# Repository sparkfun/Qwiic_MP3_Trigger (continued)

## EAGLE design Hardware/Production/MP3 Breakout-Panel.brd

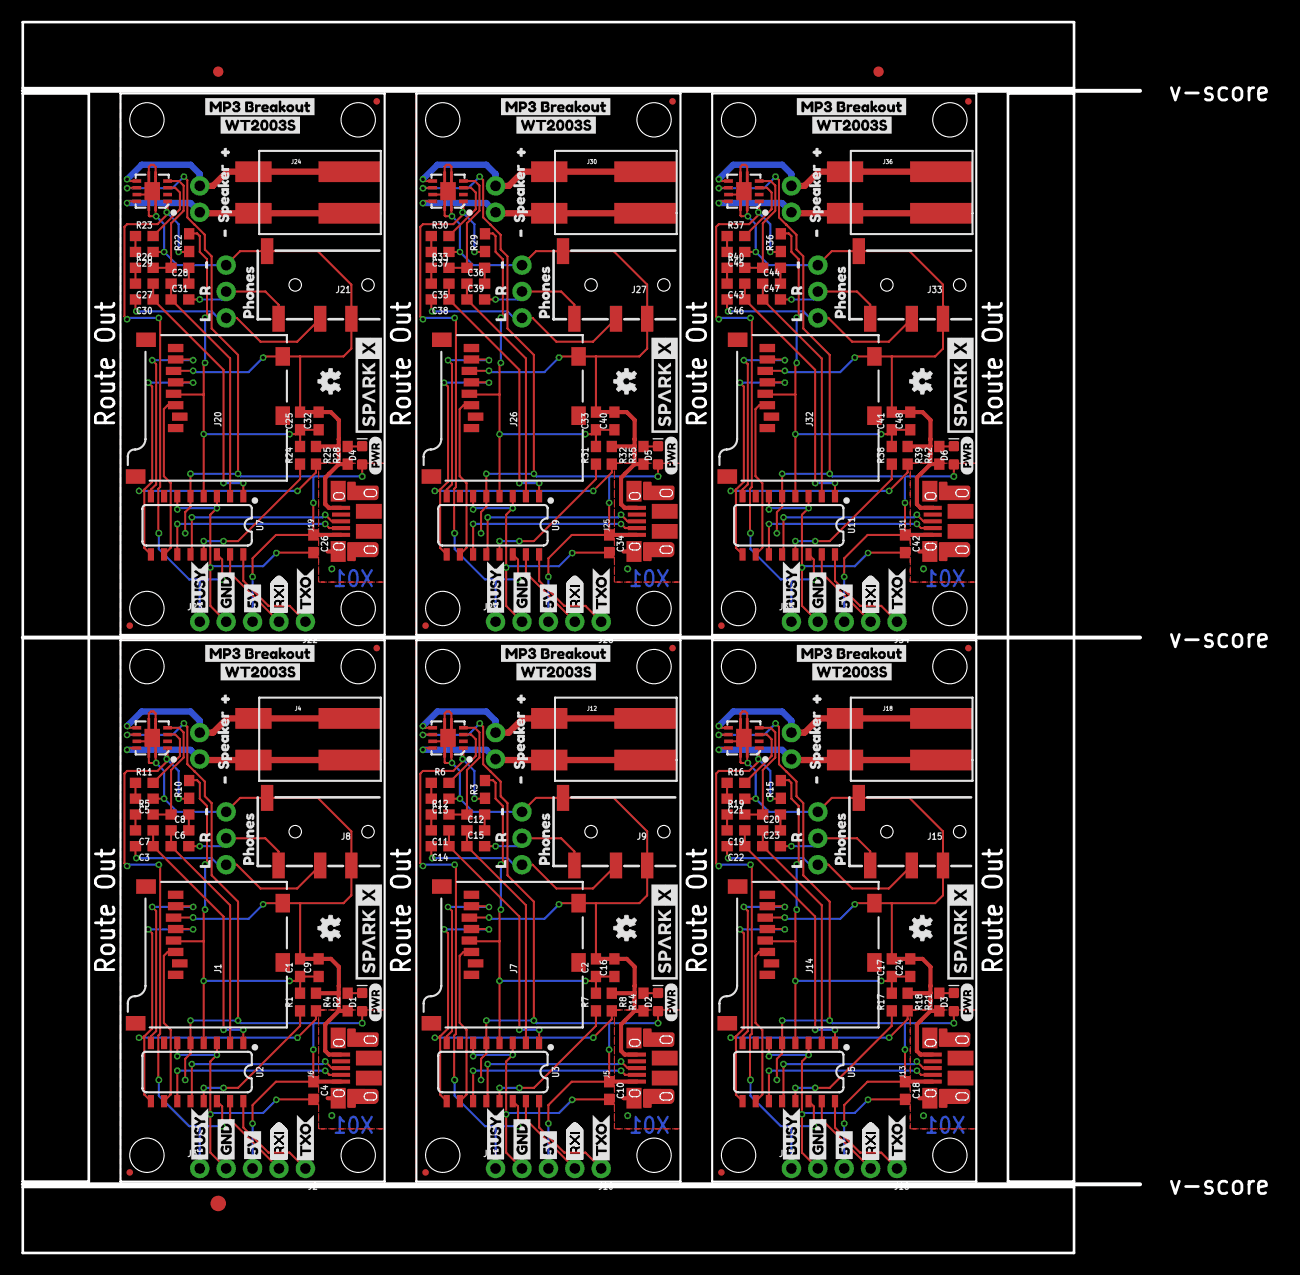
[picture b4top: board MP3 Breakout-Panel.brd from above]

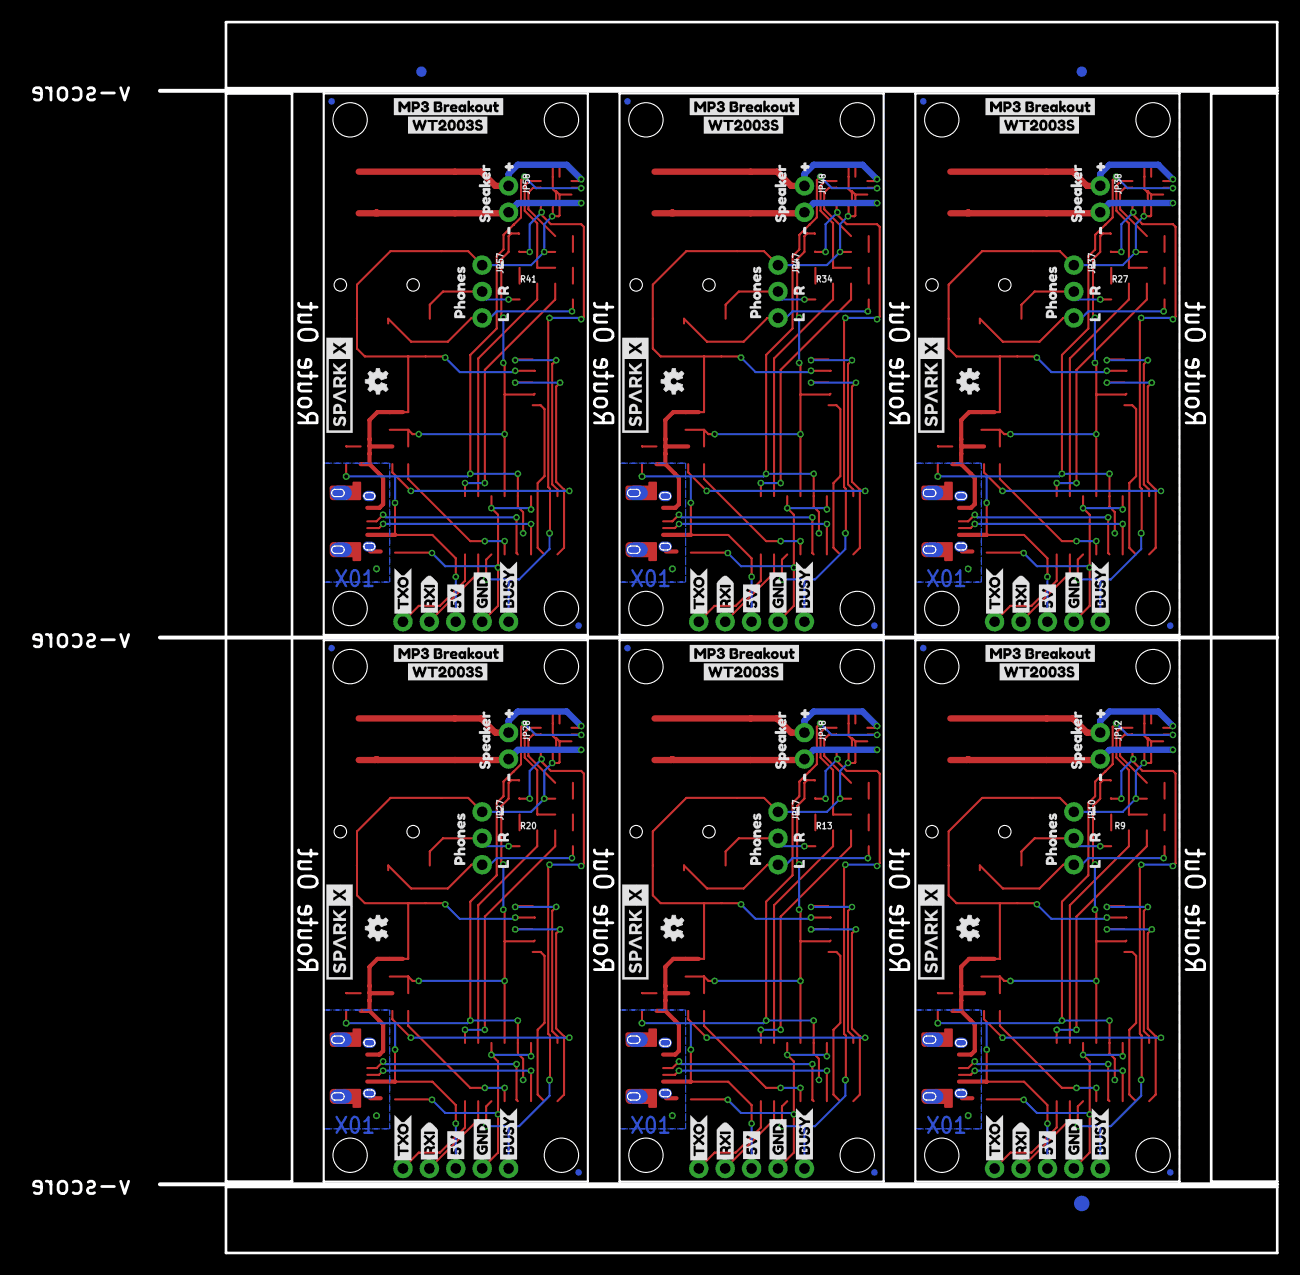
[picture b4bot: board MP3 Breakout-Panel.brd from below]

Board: 2 copper layers, 107.4 x 118.4 mm, 414 parts (123 on the bottom side), 150 nets.

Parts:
C1, C2, C17, C25, C33, C41: 10uF; 0603
C3, C6, C14, C15, C22, C23, C30, C31, C38, C39, C46, C47: 0.22uF; 0603
C4, C5, C9, C10, C13, C16, C18, C21, C24, C26, C29, C32, C34, C37, C40, C42, C45, C48: 1.0uF; 0603
C7, C8, C11, C12, C19, C20, C27, C28, C35, C36, C43, C44: 0.1uF; 0603
D1, D2, D3, D4, D5, D6: RED; LED-0603
E$1, E$2, E$3, E$4: FIDUCIAL-1X2
E$5, E$6: FIDUCIAL-1.5X3
J1, J7, J14, J20, J26, J32: MICRO-SD; MICRO-SD-SOCKET
J2, J10, J16, J22, J28, J34: Header; 1X04_NO_SILK
J3, J11, J17, J23, J29, J35: 1X01_NO_SILK
J4, J12, J18, J24, J30, J36: Poke-Home; 1X02_POKEHOME
J5, J6, J13, J19, J25, J31: USB-MICROB-PTH-MILL
J8, J9, J15, J21, J27, J33: 3.5mm Audio; AUDIO_JACK_3.5MM_TRRS_SMD_RA
JP1, JP2, JP5, JP6, JP9, JP14, JP15, JP16, JP23, JP24, JP25, JP26, JP33, JP34, JP35, JP36, JP43, JP44, JP45, JP46, JP53, JP54, JP55, JP56: FIDUCIALUFIDUCIAL; MICRO-FIDUCIAL
JP3, JP4, JP7, JP8, JP11, JP13, JP19, JP20, JP21, JP22, JP29, JP30, JP31, JP32, JP39, JP40, JP41, JP42, JP49, JP50, JP51, JP52, JP59, JP60: STAND-OFF
JP10, JP17, JP27, JP37, JP47, JP57: PTH; 1X03_NO_SILK
JP12, JP18, JP28, JP38, JP48, JP58: PTH; 1X02_NO_SILK
LOGO1, LOGO3, LOGO5, LOGO7, LOGO9, LOGO11: OSHW-LOGOMINI; OSHW-LOGO-MINI
LOGO2, LOGO4, LOGO6, LOGO8, LOGO10, LOGO12: OSHW-LOGOMINI; OSHW-LOGO-MINI@1
R1, R3, R5, R7, R9, R10, R12, R13, R15, R17, R19, R20, R22, R24, R26, R27, R29, R31, R33, R34, R36, R38, R40, R41: 10k; 0603
R2, R14, R21, R28, R35, R42: 1k; 0603
R4, R8, R18, R25, R32, R39: 2.2k; 0603
R6, R11, R16, R23, R30, R37: 100k; 0603
U1, U4, U6, U8, U10, U12: TPA2005D1; QFN-8_PAD
U2, U3, U5, U7, U9, U11: WT2003S; SO16
U$1, U$22, U$31, U$45, U$66, U$77, U$98, U$109, U$130, U$141, U$162, U$173: GND1
U$2, U$5, U$11, U$49, U$65, U$81, U$97, U$113, U$129, U$145, U$161, U$177: SPARKX-LOGO4; SPARKX-MEDIUM
U$3, U$38, U$41, U$52, U$73, U$84, U$105, U$116, U$137, U$148, U$169, U$180: L12
U$4, U$37, U$39, U$53, U$72, U$85, U$104, U$117, U$136, U$149, U$168, U$181: R11
U$6, U$9, U$43, U$48, U$75, U$80, U$107, U$112, U$139, U$144, U$171, U$176: TXO0
U$7, U$8, U$23, U$44, U$46, U$47, U$76, U$78, U$79, U$108, U$110, U$111, U$140, U$142, U$143, U$172, U$174, U$175: RXI0
U$10, U$15, U$21, U$25, U$33, U$35, U$54, U$58, U$68, U$70, U$86, U$90, U$100, U$102, U$118, U$122, U$132, U$134, U$150, U$154, U$164, U$166, U$182, U$186: #6
U$12, U$24, U$59, U$60, U$91, U$92, U$123, U$124, U$155, U$156, U$187, U$188: MP3_BREAKOUT0
U$13, U$14, U$50, U$51, U$82, U$83, U$114, U$115, U$146, U$147, U$178, U$179: BUSY0
U$16, U$40, U$42, U$55, U$74, U$87, U$106, U$119, U$138, U$151, U$170, U$183: PHONES0
U$17, U$32, U$67, U$99, U$131, U$163: PWR-()-03
U$18, U$20, U$34, U$56, U$69, U$88, U$101, U$120, U$133, U$152, U$165, U$184: SPEAKER1
U$19, U$28, U$36, U$57, U$71, U$89, U$103, U$121, U$135, U$153, U$167, U$185: #5
U$26, U$27, U$61, U$62, U$93, U$94, U$125, U$126, U$157, U$158, U$189, U$190: WT2003S0
U$29, U$30, U$63, U$64, U$95, U$96, U$127, U$128, U$159, U$160, U$191, U$192: 5V0

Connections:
5V: C4.1, D1.A, J2.3, J6.VBUS, U1.6, U2.5
5V1: C10.1, D2.A, J5.VBUS, J10.3, U3.5, U4.6
5V2: C18.1, D3.A, J13.VBUS, J16.3, U5.5, U6.6
5V3: C26.1, D4.A, J19.VBUS, J22.3, U7.5, U8.6
5V4: C34.1, D5.A, J25.VBUS, J28.3, U9.5, U10.6
5V5: C42.1, D6.A, J31.VBUS, J34.3, U11.5, U12.6
!SDN: J3.1, R10.1, U1.1, U2.14
!SDN1: J11.1, R3.1, U3.14, U4.1
!SDN2: J17.1, R15.1, U5.14, U6.1
!SDN3: J23.1, R22.1, U7.14, U8.1
!SDN4: J29.1, R29.1, U9.14, U10.1
!SDN5: J35.1, R36.1, U11.14, U12.1
AC-L: C3.2, J8.RING1, JP10.3
AC-L1: C14.2, J9.RING1, JP17.3
AC-L2: C22.2, J15.RING1, JP27.3
AC-L3: C30.2, J21.RING1, JP37.3
AC-L4: C38.2, J27.RING1, JP47.3
AC-L5: C46.2, J33.RING1, JP57.3
AC-R: C6.2, J8.TIP, JP10.2
AC-R1: C15.2, J9.TIP, JP17.2
AC-R2: C23.2, J15.TIP, JP27.2
AC-R3: C31.2, J21.TIP, JP37.2
AC-R4: C39.2, J27.TIP, JP47.2
AC-R5: C47.2, J33.TIP, JP57.2
ADKEY: R1.1, U2.13
ADKEY1: R7.1, U3.13
ADKEY2: R17.1, U5.13
ADKEY3: R24.1, U7.13
ADKEY4: R31.1, U9.13
ADKEY5: R38.1, U11.13
D+: J6.D+, U2.12
D+1: J5.D+, U3.12
D+2: J13.D+, U5.12
D+3: J19.D+, U7.12
D+4: J25.D+, U9.12
D+5: J31.D+, U11.12
D-: J6.D-, U2.11
D-1: J5.D-, U3.11
D-2: J13.D-, U5.11
D-3: J19.D-, U7.11
D-4: J25.D-, U9.11
D-5: J31.D-, U11.11
GND: C1.2, C4.2, C5.1, C9.2, J1.CD1, J1.GND, J2.4, J6.GND, J8.EARTH, J8.RING2, JP10.1, R2.1, R4.1, U1.7, U1.9, U1.10, U1.11, U1.12, U1.13, U2.3, U2.6
GND1: C2.2, C10.2, C13.1, C16.2, J5.GND, J7.CD1, J7.GND, J9.EARTH, J9.RING2, J10.4, JP17.1, R8.1, R14.1, U3.3, U3.6, U4.7, U4.9, U4.10, U4.11, U4.12, U4.13
GND2: C17.2, C18.2, C21.1, C24.2, J13.GND, J14.CD1, J14.GND, J15.EARTH, J15.RING2, J16.4, JP27.1, R18.1, R21.1, U5.3, U5.6, U6.7, U6.9, U6.10, U6.11, U6.12, U6.13
GND3: C25.2, C26.2, C29.1, C32.2, J19.GND, J20.CD1, J20.GND, J21.EARTH, J21.RING2, J22.4, JP37.1, R25.1, R28.1, U7.3, U7.6, U8.7, U8.9, U8.10, U8.11, U8.12, U8.13
GND4: C33.2, C34.2, C37.1, C40.2, J25.GND, J26.CD1, J26.GND, J27.EARTH, J27.RING2, J28.4, JP47.1, R32.1, R35.1, U9.3, U9.6, U10.7, U10.9, U10.10, U10.11, U10.12, U10.13
GND5: C41.2, C42.2, C45.1, C48.2, J31.GND, J32.CD1, J32.GND, J33.EARTH, J33.RING2, J34.4, JP57.1, R39.1, R42.1, U11.3, U11.6, U12.7, U12.9, U12.10, U12.11, U12.12, U12.13
IN+AMP: R11.2, U1.3
IN+AMP1: R6.2, U4.3
IN+AMP2: R16.2, U6.3
IN+AMP3: R23.2, U8.3
IN+AMP4: R30.2, U10.3
IN+AMP5: R37.2, U12.3
IN-AMP: R5.2, R9.2, U1.4
IN-AMP1: R12.2, R13.2, U4.4
IN-AMP2: R19.2, R20.2, U6.4
IN-AMP3: R26.2, R27.2, U8.4
IN-AMP4: R33.2, R34.2, U10.4
IN-AMP5: R40.2, R41.2, U12.4
MP3-RXI: J2.2, U2.15
MP3-RXI1: J10.2, U3.15
MP3-RXI2: J16.2, U5.15
MP3-RXI3: J22.2, U7.15
MP3-RXI4: J28.2, U9.15
MP3-RXI5: J34.2, U11.15
MP3-TXO: J2.1, U2.16
MP3-TXO1: J10.1, U3.16
MP3-TXO2: J16.1, U5.16
MP3-TXO3: J22.1, U7.16
MP3-TXO4: J28.1, U9.16
MP3-TXO5: J34.1, U11.16
unnamed: D1.C, R2.2
unnamed: C13.2, R6.1
unnamed: C11.2, R12.1
unnamed: C12.2, R13.1
unnamed: C8.2, R9.1
unnamed: D2.C, R14.2
unnamed: C21.2, R16.1
unnamed: C5.2, R11.1
unnamed: C7.2, R5.1
unnamed: C19.2, R19.1
unnamed: C20.2, R20.1
unnamed: D3.C, R21.2
unnamed: C29.2, R23.1
unnamed: C27.2, R26.1
unnamed: C28.2, R27.1
unnamed: D4.C, R28.2
unnamed: C37.2, R30.1
unnamed: C35.2, R33.1
unnamed: C36.2, R34.1
unnamed: D5.C, R35.2
unnamed: C45.2, R37.1
unnamed: C43.2, R40.1
unnamed: C44.2, R41.1
unnamed: D6.C, R42.2
OUT+: J4.P2, J4.P4, JP12.1, U1.5
OUT+1: J12.P2, J12.P4, JP18.1, U4.5
OUT+2: J18.P2, J18.P4, JP28.1, U6.5
OUT+3: J24.P2, J24.P4, JP38.1, U8.5
OUT+4: J30.P2, J30.P4, JP48.1, U10.5
OUT+5: J36.P2, J36.P4, JP58.1, U12.5
OUT-: J4.P1, J4.P3, JP12.2, U1.8
OUT-1: J12.P1, J12.P3, JP18.2, U4.8
OUT-2: J18.P1, J18.P3, JP28.2, U6.8
OUT-3: J24.P1, J24.P3, JP38.2, U8.8
OUT-4: J30.P1, J30.P3, JP48.2, U10.8
OUT-5: J36.P1, J36.P3, JP58.2, U12.8
SD_CLK: J1.SCLK, R4.2, U2.9
SD_CLK1: J7.SCLK, R8.2, U3.9
SD_CLK2: J14.SCLK, R18.2, U5.9
SD_CLK3: J20.SCLK, R25.2, U7.9
SD_CLK4: J26.SCLK, R32.2, U9.9
SD_CLK5: J32.SCLK, R39.2, U11.9
SD_CMD: J1.DI, U2.10
SD_CMD1: J7.DI, U3.10
SD_CMD2: J14.DI, U5.10
SD_CMD3: J20.DI, U7.10
SD_CMD4: J26.DI, U9.10
SD_CMD5: J32.DI, U11.10
SD_DAT: J1.DO, U2.8
SD_DAT1: J7.DO, U3.8
SD_DAT2: J14.DO, U5.8
SD_DAT3: J20.DO, U7.8
SD_DAT4: J26.DO, U9.8
SD_DAT5: J32.DO, U11.8
SHLD: J6.SHIELD, J6.SHIELD2, J6.SHIELD3, J6.SHIELD4, J6.SHIELD5, J6.SHIELD6, J6.SHIELD7, J6.SHIELD8, J6.SHIELD9, J6.SHIELD10
SHLD1: J5.SHIELD, J5.SHIELD2, J5.SHIELD3, J5.SHIELD4, J5.SHIELD5, J5.SHIELD6, J5.SHIELD7, J5.SHIELD8, J5.SHIELD9, J5.SHIELD10
SHLD2: J13.SHIELD, J13.SHIELD2, J13.SHIELD3, J13.SHIELD4, J13.SHIELD5, J13.SHIELD6, J13.SHIELD7, J13.SHIELD8, J13.SHIELD9, J13.SHIELD10
SHLD3: J19.SHIELD, J19.SHIELD2, J19.SHIELD3, J19.SHIELD4, J19.SHIELD5, J19.SHIELD6, J19.SHIELD7, J19.SHIELD8, J19.SHIELD9, J19.SHIELD10
SHLD4: J25.SHIELD, J25.SHIELD2, J25.SHIELD3, J25.SHIELD4, J25.SHIELD5, J25.SHIELD6, J25.SHIELD7, J25.SHIELD8, J25.SHIELD9, J25.SHIELD10
SHLD5: J31.SHIELD, J31.SHIELD2, J31.SHIELD3, J31.SHIELD4, J31.SHIELD5, J31.SHIELD6, J31.SHIELD7, J31.SHIELD8, J31.SHIELD9, J31.SHIELD10
VCCIO: C1.1, C9.1, J1.VCC, R1.2, R10.2, U2.4
VCCIO1: C2.1, C16.1, J7.VCC, R3.2, R7.2, U3.4
VCCIO2: C17.1, C24.1, J14.VCC, R15.2, R17.2, U5.4
VCCIO3: C25.1, C32.1, J20.VCC, R22.2, R24.2, U7.4
VCCIO4: C33.1, C40.1, J26.VCC, R29.2, R31.2, U9.4
VCCIO5: C41.1, C48.1, J32.VCC, R36.2, R38.2, U11.4
VOUTL: C3.1, C7.1, U2.1
VOUTL1: C11.1, C14.1, U3.1
VOUTL2: C19.1, C22.1, U5.1
VOUTL3: C27.1, C30.1, U7.1
VOUTL4: C35.1, C38.1, U9.1
VOUTL5: C43.1, C46.1, U11.1
VOUTR: C6.1, C8.1, U2.2
VOUTR1: C12.1, C15.1, U3.2
VOUTR2: C20.1, C23.1, U5.2
VOUTR3: C28.1, C31.1, U7.2
VOUTR4: C36.1, C39.1, U9.2
VOUTR5: C44.1, C47.1, U11.2

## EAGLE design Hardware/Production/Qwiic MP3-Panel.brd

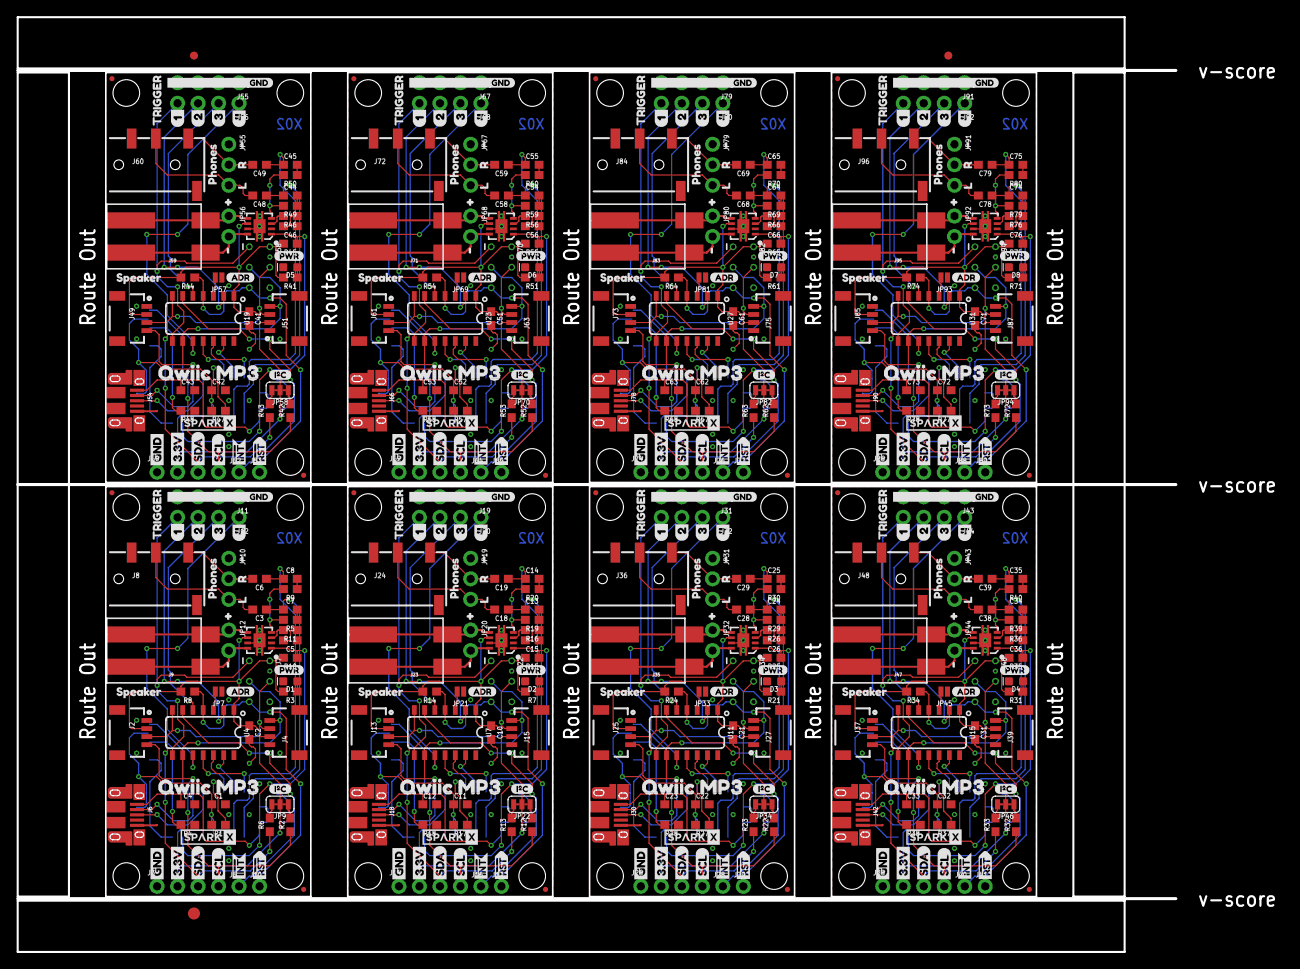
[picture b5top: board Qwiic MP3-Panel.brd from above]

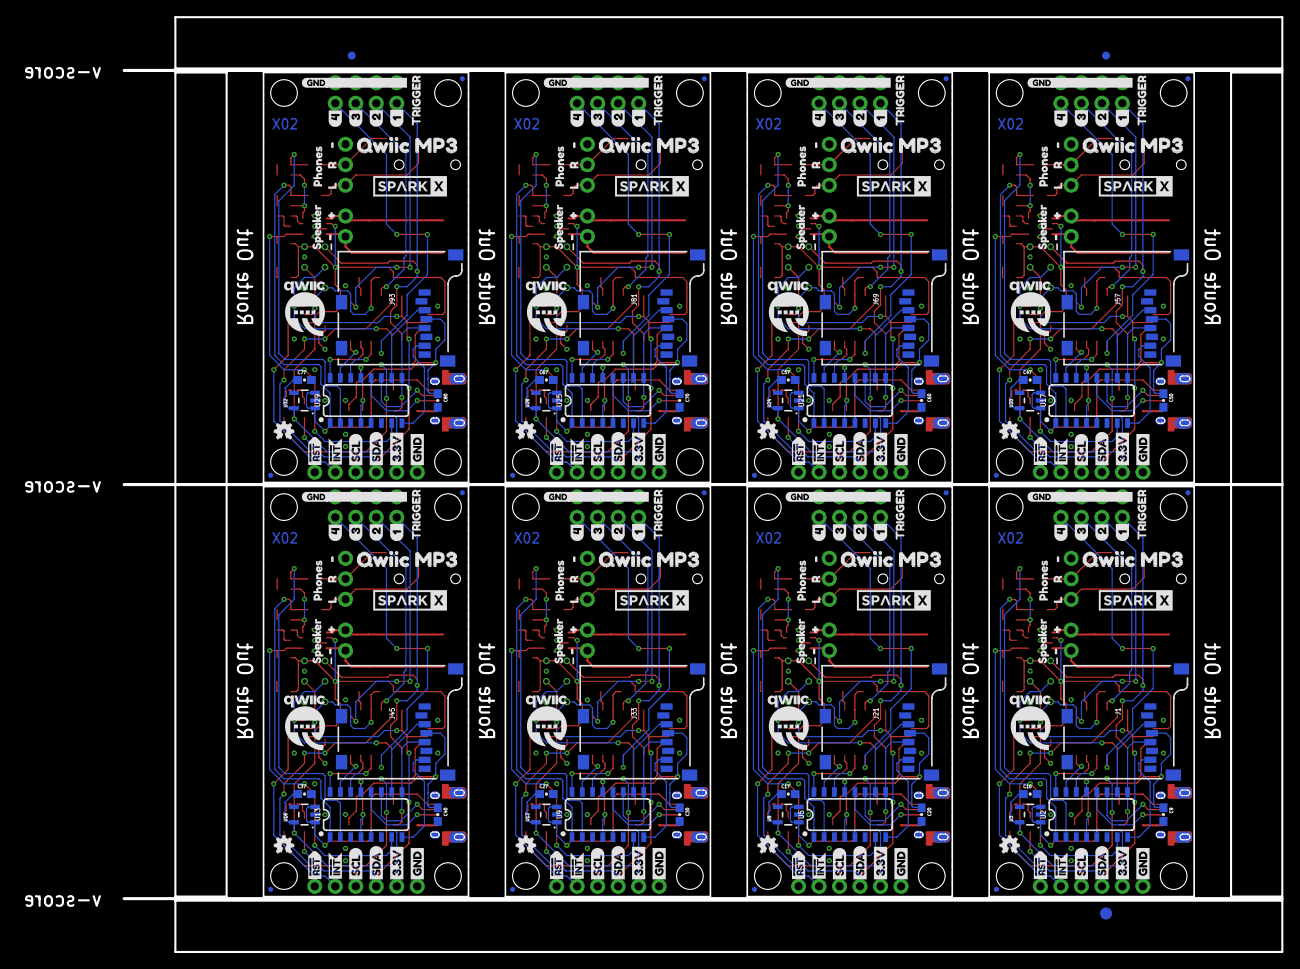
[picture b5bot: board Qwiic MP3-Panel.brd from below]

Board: 2 copper layers, 143.5 x 115.8 mm, 774 parts (243 on the bottom side), 296 nets.

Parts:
C1, C3, C6, C11, C18, C19, C22, C28, C29, C32, C38, C39, C42, C48, C49, C52, C58, C59, C62, C68, C69, C72, C78, C79: 10uF; 0603
C2, C7, C8, C10, C13, C14, C21, C24, C25, C31, C34, C35, C41, C44, C45, C51, C54, C55, C61, C64, C65, C71, C74, C75: 0.1uF; 0603
C4, C5, C12, C15, C23, C26, C33, C36, C43, C46, C53, C56, C63, C66, C73, C76: 1.0uF; 0603
C9, C16, C17, C20, C27, C30, C37, C40, C47, C50, C57, C60, C67, C70, C77, C80: 1.0uF; 0603-CAP
D1, D2, D3, D4, D5, D6, D7, D8: RED; LED-0603
E$1, E$2, E$3, E$4: FIDUCIAL-1X2
E$5, E$6: FIDUCIAL-1.5X3
J1, J21, J33, J45, J57, J69, J81, J93: MICRO-SD; MICRO-SD-SOCKET
J2, J4, J13, J15, J25, J27, J37, J39, J49, J51, J61, J63, J73, J75, J85, J87: 1X04_1MM_RA
J3, J14, J26, J38, J50, J62, J74, J86: PTH; 1X04_NO_SILK
J5, J10, J16, J17, J28, J29, J40, J41, J52, J53, J64, J65, J76, J77, J88, J89: 1X01_NO_SILK
J6, J18, J30, J42, J54, J66, J78, J90: USB-MICROB-PTH-MILL
J7, J22, J34, J46, J58, J70, J82, J94: ISP; 2X3_TEST_POINTS
J8, J24, J36, J48, J60, J72, J84, J96: 3.5mm Audio; AUDIO_JACK_3.5MM_TRRS_SMD_RA
J9, J23, J35, J47, J59, J71, J83, J95: Poke-Home; 1X02_POKEHOME
J11, J12, J19, J20, J31, J32, J43, J44, J55, J56, J67, J68, J79, J80, J91, J92: 1X04_NO_SILK
JP1, JP2, JP5, JP6, JP15, JP16, JP17, JP18, JP27, JP28, JP29, JP30, JP39, JP40, JP41, JP42, JP51, JP52, JP53, JP54, JP63, JP64, JP65, JP66, JP75, JP76, JP77, JP78, JP87, JP88, JP89, JP90: FIDUCIALUFIDUCIAL; MICRO-FIDUCIAL
JP3, JP4, JP8, JP11, JP13, JP14, JP23, JP24, JP25, JP26, JP35, JP36, JP37, JP38, JP47, JP48, JP49, JP50, JP59, JP60, JP61, JP62, JP71, JP72, JP73, JP74, JP83, JP84, JP85, JP86, JP95, JP96: STAND-OFF
JP7, JP21, JP33, JP45, JP57, JP69, JP81, JP93: ADR; SMT-JUMPER_2_NO_NO-SILK
JP9, JP22, JP34, JP46, JP58, JP70, JP82, JP94: SMT-JUMPER_3_2-NC_TRACE_SILK
JP10, JP19, JP31, JP43, JP55, JP67, JP79, JP91: PTH; 1X03_NO_SILK
JP12, JP20, JP32, JP44, JP56, JP68, JP80, JP92: PTH; 1X02_NO_SILK
LOGO1, LOGO2, LOGO3, LOGO4, LOGO5, LOGO6, LOGO7, LOGO8: OSHW-LOGOMINI; OSHW-LOGO-MINI
R1, R5, R9, R10, R15, R17, R19, R20, R25, R27, R29, R30, R35, R37, R39, R40, R45, R47, R49, R50, R55, R57, R59, R60, R65, R67, R69, R70, R75, R77, R79, R80: 10k; 0603
R2, R4, R6, R12, R13, R18, R22, R23, R28, R32, R33, R38, R42, R43, R48, R52, R53, R58, R62, R63, R68, R72, R73, R78: 2.2k; 0603
R3, R7, R21, R31, R41, R51, R61, R71: 1k; 0603
R8, R14, R24, R34, R44, R54, R64, R74: 4.7k; 0603
R11, R16, R26, R36, R46, R56, R66, R76: 100k; 0603
U1, U6, U10, U14, U18, U22, U26, U30: TPA2005D1; QFN-8_PAD
U2, U5, U9, U13, U17, U21, U25, U29: WT2003S; SO16
U3, U8, U12, U16, U20, U24, U28, U32: AP2112-3.3V; SOT23-5
U4, U7, U11, U15, U19, U23, U27, U31: ATTINY84-ARDUINO; SO14
U$1, U$48, U$94, U$140, U$186, U$232, U$278, U$324: SPARKX-LOGO3; SPARKX-SMALL
U$2, U$30, U$93, U$139, U$185, U$231, U$277, U$323: SPARKX-LOGO4; SPARKX-MEDIUM
U$3, U$22, U$50, U$53, U$96, U$99, U$142, U$145, U$188, U$191, U$234, U$237, U$280, U$283, U$326, U$329: GND1
U$4, U$21, U$49, U$54, U$95, U$100, U$141, U$146, U$187, U$192, U$233, U$238, U$279, U$284, U$325, U$330: 3#3V2
U$5, U$27, U$52, U$55, U$98, U$101, U$144, U$147, U$190, U$193, U$236, U$239, U$282, U$285, U$328, U$331: SDA8
U$6, U$26, U$51, U$56, U$97, U$102, U$143, U$148, U$189, U$194, U$235, U$240, U$281, U$286, U$327, U$332: SCL9
U$7, U$16, U$60, U$61, U$106, U$107, U$152, U$153, U$198, U$199, U$244, U$245, U$290, U$291, U$336, U$337: RST#-[>
U$8, U$57, U$103, U$149, U$195, U$241, U$287, U$333: I_SUPER2_C-()-03
U$9, U$11, U$58, U$59, U$104, U$105, U$150, U$151, U$196, U$197, U$242, U$243, U$288, U$289, U$334, U$335: INT#-[<
U$10, U$13, U$25, U$38, U$69, U$74, U$79, U$83, U$115, U$120, U$125, U$129, U$161, U$166, U$171, U$175, U$207, U$212, U$217, U$221, U$253, U$258, U$263, U$267, U$299, U$304, U$309, U$313, U$345, U$350, U$355, U$359: #6
U$12, U$28, U$68, U$80, U$114, U$126, U$160, U$172, U$206, U$218, U$252, U$264, U$298, U$310, U$344, U$356: #5
U$14, U$20, U$76, U$91, U$122, U$137, U$168, U$183, U$214, U$229, U$260, U$275, U$306, U$321, U$352, U$367: SPEAKER1
U$15, U$40, U$75, U$90, U$121, U$136, U$167, U$182, U$213, U$228, U$259, U$274, U$305, U$320, U$351, U$366: PHONES0
U$17, U$62, U$108, U$154, U$200, U$246, U$292, U$338: PWR-()-03
U$18, U$63, U$109, U$155, U$201, U$247, U$293, U$339: ADR-()-03
U$19, U$44, U$70, U$87, U$116, U$133, U$162, U$179, U$208, U$225, U$254, U$271, U$300, U$317, U$346, U$363: 1_1
U$23, U$24, U$77, U$78, U$123, U$124, U$169, U$170, U$215, U$216, U$261, U$262, U$307, U$308, U$353, U$354: QWIIC_MP32
U$29, U$45, U$64, U$88, U$110, U$134, U$156, U$180, U$202, U$226, U$248, U$272, U$294, U$318, U$340, U$364: TRIGGER5
U$31, U$34, U$67, U$81, U$113, U$127, U$159, U$173, U$205, U$219, U$251, U$265, U$297, U$311, U$343, U$357: 43
U$32, U$42, U$65, U$86, U$111, U$132, U$157, U$178, U$203, U$224, U$249, U$270, U$295, U$316, U$341, U$362: 21
U$33, U$36, U$66, U$82, U$112, U$128, U$158, U$174, U$204, U$220, U$250, U$266, U$296, U$312, U$342, U$358: 32
U$35, U$46, U$71, U$89, U$117, U$135, U$163, U$181, U$209, U$227, U$255, U$273, U$301, U$319, U$347, U$365: GND0
U$37, U$41, U$72, U$85, U$118, U$131, U$164, U$177, U$210, U$223, U$256, U$269, U$302, U$315, U$348, U$361: L12
U$39, U$43, U$73, U$84, U$119, U$130, U$165, U$176, U$211, U$222, U$257, U$268, U$303, U$314, U$349, U$360: R11
U$47, U$92, U$138, U$184, U$230, U$276, U$322, U$368: QWIIC-LOGO-MEDIUM

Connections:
3.3V: C2.1, C16.1, J2.2, J3.2, J4.2, J7.2, JP9.2, R3.2, R8.2, R10.2, U1.6, U2.5, U3.5, U4.1
3.3V1: C10.1, C17.1, J13.2, J14.2, J15.2, J22.2, JP22.2, R7.2, R14.2, R15.2, U5.5, U6.6, U7.1, U8.5
3.3V2: C21.1, C27.1, J25.2, J26.2, J27.2, J34.2, JP34.2, R21.2, R24.2, R25.2, U9.5, U10.6, U11.1, U12.5
3.3V3: C31.1, C37.1, J37.2, J38.2, J39.2, J46.2, JP46.2, R31.2, R34.2, R35.2, U13.5, U14.6, U15.1, U16.5
3.3V4: C41.1, C47.1, J49.2, J50.2, J51.2, J58.2, JP58.2, R41.2, R44.2, R45.2, U17.5, U18.6, U19.1, U20.5
3.3V5: C51.1, C57.1, J61.2, J62.2, J63.2, J70.2, JP70.2, R51.2, R54.2, R55.2, U21.5, U22.6, U23.1, U24.5
3.3V6: C61.1, C67.1, J73.2, J74.2, J75.2, J82.2, JP82.2, R61.2, R64.2, R65.2, U25.5, U26.6, U27.1, U28.5
3.3V7: C71.1, C77.1, J85.2, J86.2, J87.2, J94.2, JP94.2, R71.2, R74.2, R75.2, U29.5, U30.6, U31.1, U32.5
5V: C4.1, J6.VBUS, U3.1, U3.3
5V1: C12.1, J18.VBUS, U8.1, U8.3
5V2: C23.1, J30.VBUS, U12.1, U12.3
5V3: C33.1, J42.VBUS, U16.1, U16.3
5V4: C43.1, J54.VBUS, U20.1, U20.3
5V5: C53.1, J66.VBUS, U24.1, U24.3
5V6: C63.1, J78.VBUS, U28.1, U28.3
5V7: C73.1, J90.VBUS, U32.1, U32.3
!INT: J5.1, U4.6
!INT1: J16.1, U7.6
!INT2: J28.1, U11.6
!INT3: J40.1, U15.6
!INT4: J52.1, U19.6
!INT5: J64.1, U23.6
!INT6: J76.1, U27.6
!INT7: J88.1, U31.6
!RST: J7.5, J10.1, R8.1, U4.4
!RST1: J17.1, J22.5, R14.1, U7.4
!RST2: J29.1, J34.5, R24.1, U11.4
!RST3: J41.1, J46.5, R34.1, U15.4
!RST4: J53.1, J58.5, R44.1, U19.4
!RST5: J65.1, J70.5, R54.1, U23.4
!RST6: J77.1, J82.5, R64.1, U27.4
!RST7: J89.1, J94.5, R74.1, U31.4
!SDN: R10.1, U1.1, U2.7
!SDN1: R15.1, U5.7, U6.1
!SDN2: R25.1, U9.7, U10.1
!SDN3: R35.1, U13.7, U14.1
!SDN4: R45.1, U17.7, U18.1
!SDN5: R55.1, U21.7, U22.1
!SDN6: R65.1, U25.7, U26.1
!SDN7: R75.1, U29.7, U30.1
AC-L: C3.2, J8.RING1, JP10.3
AC-L1: C18.2, J24.RING1, JP19.3
AC-L2: C28.2, J36.RING1, JP31.3
AC-L3: C38.2, J48.RING1, JP43.3
AC-L4: C48.2, J60.RING1, JP55.3
AC-L5: C58.2, J72.RING1, JP67.3
AC-L6: C68.2, J84.RING1, JP79.3
AC-L7: C78.2, J96.RING1, JP91.3
AC-R: C6.2, J8.TIP, JP10.2
AC-R1: C19.2, J24.TIP, JP19.2
AC-R2: C29.2, J36.TIP, JP31.2
AC-R3: C39.2, J48.TIP, JP43.2
AC-R4: C49.2, J60.TIP, JP55.2
AC-R5: C59.2, J72.TIP, JP67.2
AC-R6: C69.2, J84.TIP, JP79.2
AC-R7: C79.2, J96.TIP, JP91.2
ADKEY: R1.1, U2.13
ADKEY1: R17.1, U5.13
ADKEY2: R27.1, U9.13
ADKEY3: R37.1, U13.13
ADKEY4: R47.1, U17.13
ADKEY5: R57.1, U21.13
ADKEY6: R67.1, U25.13
ADKEY7: R77.1, U29.13
ADR: JP7.2, U4.3
ADR1: JP21.2, U7.3
ADR2: JP33.2, U11.3
ADR3: JP45.2, U15.3
ADR4: JP57.2, U19.3
ADR5: JP69.2, U23.3
ADR6: JP81.2, U27.3
ADR7: JP93.2, U31.3
D+: J6.D+, U2.12
D+1: J18.D+, U5.12
D+2: J30.D+, U9.12
D+3: J42.D+, U13.12
D+4: J54.D+, U17.12
D+5: J66.D+, U21.12
D+6: J78.D+, U25.12
D+7: J90.D+, U29.12
D-: J6.D-, U2.11
D-1: J18.D-, U5.11
D-2: J30.D-, U9.11
D-3: J42.D-, U13.11
D-4: J54.D-, U17.11
D-5: J66.D-, U21.11
D-6: J78.D-, U25.11
D-7: J90.D-, U29.11
GND: C1.2, C2.2, C4.2, C5.1, C9.2, C16.2, D1.C, J1.CD1, J1.GND, J2.1, J3.1, J4.1, J6.GND, J6.SHIELD, J6.SHIELD2, J6.SHIELD3, J6.SHIELD4, J6.SHIELD5, J6.SHIELD6, J6.SHIELD7, J6.SHIELD8, J6.SHIELD9, J6.SHIELD10, J7.6, J8.EARTH, J8.RING2, J11.1, J11.2, J11.3, J11.4, JP7.1, JP10.1, R4.1, U1.7, U1.9, U1.10, U1.11, U1.12, U1.13, U2.3, U2.6, U3.2, U4.14
GND1: C10.2, C11.2, C12.2, C15.1, C17.2, C20.2, D2.C, J13.1, J14.1, J15.1, J18.GND, J18.SHIELD, J18.SHIELD2, J18.SHIELD3, J18.SHIELD4, J18.SHIELD5, J18.SHIELD6, J18.SHIELD7, J18.SHIELD8, J18.SHIELD9, J18.SHIELD10, J19.1, J19.2, J19.3, J19.4, J21.CD1, J21.GND, J22.6, J24.EARTH, J24.RING2, JP19.1, JP21.1, R18.1, U5.3, U5.6, U6.7, U6.9, U6.10, U6.11, U6.12, U6.13, U7.14, U8.2
GND2: C21.2, C22.2, C23.2, C26.1, C27.2, C30.2, D3.C, J25.1, J26.1, J27.1, J30.GND, J30.SHIELD, J30.SHIELD2, J30.SHIELD3, J30.SHIELD4, J30.SHIELD5, J30.SHIELD6, J30.SHIELD7, J30.SHIELD8, J30.SHIELD9, J30.SHIELD10, J31.1, J31.2, J31.3, J31.4, J33.CD1, J33.GND, J34.6, J36.EARTH, J36.RING2, JP31.1, JP33.1, R28.1, U9.3, U9.6, U10.7, U10.9, U10.10, U10.11, U10.12, U10.13, U11.14, U12.2
GND3: C31.2, C32.2, C33.2, C36.1, C37.2, C40.2, D4.C, J37.1, J38.1, J39.1, J42.GND, J42.SHIELD, J42.SHIELD2, J42.SHIELD3, J42.SHIELD4, J42.SHIELD5, J42.SHIELD6, J42.SHIELD7, J42.SHIELD8, J42.SHIELD9, J42.SHIELD10, J43.1, J43.2, J43.3, J43.4, J45.CD1, J45.GND, J46.6, J48.EARTH, J48.RING2, JP43.1, JP45.1, R38.1, U13.3, U13.6, U14.7, U14.9, U14.10, U14.11, U14.12, U14.13, U15.14, U16.2
GND4: C41.2, C42.2, C43.2, C46.1, C47.2, C50.2, D5.C, J49.1, J50.1, J51.1, J54.GND, J54.SHIELD, J54.SHIELD2, J54.SHIELD3, J54.SHIELD4, J54.SHIELD5, J54.SHIELD6, J54.SHIELD7, J54.SHIELD8, J54.SHIELD9, J54.SHIELD10, J55.1, J55.2, J55.3, J55.4, J57.CD1, J57.GND, J58.6, J60.EARTH, J60.RING2, JP55.1, JP57.1, R48.1, U17.3, U17.6, U18.7, U18.9, U18.10, U18.11, U18.12, U18.13, U19.14, U20.2
GND5: C51.2, C52.2, C53.2, C56.1, C57.2, C60.2, D6.C, J61.1, J62.1, J63.1, J66.GND, J66.SHIELD, J66.SHIELD2, J66.SHIELD3, J66.SHIELD4, J66.SHIELD5, J66.SHIELD6, J66.SHIELD7, J66.SHIELD8, J66.SHIELD9, J66.SHIELD10, J67.1, J67.2, J67.3, J67.4, J69.CD1, J69.GND, J70.6, J72.EARTH, J72.RING2, JP67.1, JP69.1, R58.1, U21.3, U21.6, U22.7, U22.9, U22.10, U22.11, U22.12, U22.13, U23.14, U24.2
GND6: C61.2, C62.2, C63.2, C66.1, C67.2, C70.2, D7.C, J73.1, J74.1, J75.1, J78.GND, J78.SHIELD, J78.SHIELD2, J78.SHIELD3, J78.SHIELD4, J78.SHIELD5, J78.SHIELD6, J78.SHIELD7, J78.SHIELD8, J78.SHIELD9, J78.SHIELD10, J79.1, J79.2, J79.3, J79.4, J81.CD1, J81.GND, J82.6, J84.EARTH, J84.RING2, JP79.1, JP81.1, R68.1, U25.3, U25.6, U26.7, U26.9, U26.10, U26.11, U26.12, U26.13, U27.14, U28.2
GND7: C71.2, C72.2, C73.2, C76.1, C77.2, C80.2, D8.C, J85.1, J86.1, J87.1, J90.GND, J90.SHIELD, J90.SHIELD2, J90.SHIELD3, J90.SHIELD4, J90.SHIELD5, J90.SHIELD6, J90.SHIELD7, J90.SHIELD8, J90.SHIELD9, J90.SHIELD10, J91.1, J91.2, J91.3, J91.4, J93.CD1, J93.GND, J94.6, J96.EARTH, J96.RING2, JP91.1, JP93.1, R78.1, U29.3, U29.6, U30.7, U30.9, U30.10, U30.11, U30.12, U30.13, U31.14, U32.2
IN+AMP: R11.2, U1.3
IN+AMP1: R16.2, U6.3
IN+AMP2: R26.2, U10.3
IN+AMP3: R36.2, U14.3
IN+AMP4: R46.2, U18.3
IN+AMP5: R56.2, U22.3
IN+AMP6: R66.2, U26.3
IN+AMP7: R76.2, U30.3
IN-AMP: R5.2, R9.2, U1.4
IN-AMP1: R19.2, R20.2, U6.4
IN-AMP2: R29.2, R30.2, U10.4
IN-AMP3: R39.2, R40.2, U14.4
IN-AMP4: R49.2, R50.2, U18.4
IN-AMP5: R59.2, R60.2, U22.4
IN-AMP6: R69.2, R70.2, U26.4
IN-AMP7: R79.2, R80.2, U30.4
MP3-RXI: U2.15, U4.13
MP3-RXI1: U5.15, U7.13
MP3-RXI2: U9.15, U11.13
MP3-RXI3: U13.15, U15.13
MP3-RXI4: U17.15, U19.13
MP3-RXI5: U21.15, U23.13
MP3-RXI6: U25.15, U27.13
MP3-RXI7: U29.15, U31.13
MP3-TXO: U2.16, U4.12
MP3-TXO1: U5.16, U7.12
MP3-TXO2: U9.16, U11.12
MP3-TXO3: U13.16, U15.12
MP3-TXO4: U17.16, U19.12
MP3-TXO5: U21.16, U23.12
MP3-TXO6: U25.16, U27.12
MP3-TXO7: U29.16, U31.12
unnamed: D2.A, R7.1
unnamed: C15.2, R16.1
unnamed: D1.A, R3.1
unnamed: C13.2, R19.1
unnamed: C8.2, R9.1
unnamed: C14.2, R20.1
unnamed: D3.A, R21.1
unnamed: C5.2, R11.1
unnamed: C7.2, R5.1
unnamed: C26.2, R26.1
unnamed: C24.2, R29.1
unnamed: C25.2, R30.1
unnamed: D4.A, R31.1
unnamed: C36.2, R36.1
unnamed: C34.2, R39.1
unnamed: C35.2, R40.1
unnamed: D5.A, R41.1
unnamed: C46.2, R46.1
unnamed: C44.2, R49.1
unnamed: C45.2, R50.1
unnamed: D6.A, R51.1
unnamed: C56.2, R56.1
unnamed: C54.2, R59.1
unnamed: C55.2, R60.1
unnamed: D7.A, R61.1
unnamed: C66.2, R66.1
unnamed: C64.2, R69.1
unnamed: C65.2, R70.1
unnamed: D8.A, R71.1
unnamed: C76.2, R76.1
unnamed: C74.2, R79.1
unnamed: C75.2, R80.1
OUT+: J9.P1, J9.P3, JP12.1, U1.5
OUT+1: J23.P1, J23.P3, JP20.1, U6.5
OUT+2: J35.P1, J35.P3, JP32.1, U10.5
OUT+3: J47.P1, J47.P3, JP44.1, U14.5
OUT+4: J59.P1, J59.P3, JP56.1, U18.5
OUT+5: J71.P1, J71.P3, JP68.1, U22.5
OUT+6: J83.P1, J83.P3, JP80.1, U26.5
OUT+7: J95.P1, J95.P3, JP92.1, U30.5
OUT-: J9.P2, J9.P4, JP12.2, U1.8
OUT-1: J23.P2, J23.P4, JP20.2, U6.8
OUT-2: J35.P2, J35.P4, JP32.2, U10.8
OUT-3: J47.P2, J47.P4, JP44.2, U14.8
OUT-4: J59.P2, J59.P4, JP56.2, U18.8
OUT-5: J71.P2, J71.P4, JP68.2, U22.8
OUT-6: J83.P2, J83.P4, JP80.2, U26.8
OUT-7: J95.P2, J95.P4, JP92.2, U30.8
PLAYING: U2.14, U4.11
PLAYING1: U5.14, U7.11
PLAYING2: U9.14, U11.11
PLAYING3: U13.14, U15.11
PLAYING4: U17.14, U19.11
PLAYING5: U21.14, U23.11
PLAYING6: U25.14, U27.11
PLAYING7: U29.14, U31.11
SCL: J2.4, J3.4, J4.4, J7.3, R2.1, U4.9
SCL1: J13.4, J14.4, J15.4, J22.3, R12.1, U7.9
SCL2: J25.4, J26.4, J27.4, J34.3, R22.1, U11.9
SCL3: J37.4, J38.4, J39.4, J46.3, R32.1, U15.9
SCL4: J49.4, J50.4, J51.4, J58.3, R42.1, U19.9
SCL5: J61.4, J62.4, J63.4, J70.3, R52.1, U23.9
SCL6: J73.4, J74.4, J75.4, J82.3, R62.1, U27.9
SCL7: J85.4, J86.4, J87.4, J94.3, R72.1, U31.9
SCL_PU1: JP9.1, R2.2
SCL_PU2: JP22.1, R12.2
SCL_PU3: JP34.1, R22.2
SCL_PU4: JP46.1, R32.2
SCL_PU5: JP58.1, R42.2
SCL_PU6: JP70.1, R52.2
SCL_PU7: JP82.1, R62.2
SCL_PU8: JP94.1, R72.2
SDA: J2.3, J3.3, J4.3, J7.4, R6.1, U4.7
SDA1: J13.3, J14.3, J15.3, J22.4, R13.1, U7.7
SDA2: J25.3, J26.3, J27.3, J34.4, R23.1, U11.7
SDA3: J37.3, J38.3, J39.3, J46.4, R33.1, U15.7
SDA4: J49.3, J50.3, J51.3, J58.4, R43.1, U19.7
SDA5: J61.3, J62.3, J63.3, J70.4, R53.1, U23.7
SDA6: J73.3, J74.3, J75.3, J82.4, R63.1, U27.7
SDA7: J85.3, J86.3, J87.3, J94.4, R73.1, U31.7
SDA_PU1: JP9.3, R6.2
SDA_PU2: JP22.3, R13.2
SDA_PU3: JP34.3, R23.2
SDA_PU4: JP46.3, R33.2
SDA_PU5: JP58.3, R43.2
SDA_PU6: JP70.3, R53.2
SDA_PU7: JP82.3, R63.2
SDA_PU8: JP94.3, R73.2
SD_CLK: J1.SCLK, R4.2, U2.9
SD_CLK1: J21.SCLK, R18.2, U5.9
SD_CLK2: J33.SCLK, R28.2, U9.9
SD_CLK3: J45.SCLK, R38.2, U13.9
SD_CLK4: J57.SCLK, R48.2, U17.9
SD_CLK5: J69.SCLK, R58.2, U21.9
SD_CLK6: J81.SCLK, R68.2, U25.9
SD_CLK7: J93.SCLK, R78.2, U29.9
SD_CMD: J1.DI, U2.10
SD_CMD1: J21.DI, U5.10
SD_CMD2: J33.DI, U9.10
SD_CMD3: J45.DI, U13.10
SD_CMD4: J57.DI, U17.10
SD_CMD5: J69.DI, U21.10
SD_CMD6: J81.DI, U25.10
SD_CMD7: J93.DI, U29.10
SD_DAT: J1.DO, U2.8
SD_DAT1: J21.DO, U5.8
SD_DAT2: J33.DO, U9.8
SD_DAT3: J45.DO, U13.8
SD_DAT4: J57.DO, U17.8
SD_DAT5: J69.DO, U21.8
SD_DAT6: J81.DO, U25.8
SD_DAT7: J93.DO, U29.8
TRIGGER1: J7.1, J12.4, U4.8
TRIGGER2: J12.3, U4.2
TRIGGER3: J12.2, U4.5
TRIGGER4: J12.1, U4.10
TRIGGER5: J20.1, U7.10
TRIGGER6: J20.4, J22.1, U7.8
TRIGGER7: J20.3, U7.2
TRIGGER8: J20.2, U7.5
TRIGGER9: J32.1, U11.10
TRIGGER10: J32.4, J34.1, U11.8
TRIGGER11: J32.3, U11.2
TRIGGER12: J32.2, U11.5
TRIGGER13: J44.1, U15.10
TRIGGER14: J44.4, J46.1, U15.8
TRIGGER15: J44.3, U15.2
TRIGGER16: J44.2, U15.5
TRIGGER17: J56.1, U19.10
TRIGGER18: J56.4, J58.1, U19.8
TRIGGER19: J56.3, U19.2
TRIGGER20: J56.2, U19.5
TRIGGER21: J68.1, U23.10
TRIGGER22: J68.4, J70.1, U23.8
TRIGGER23: J68.3, U23.2
TRIGGER24: J68.2, U23.5
TRIGGER25: J80.1, U27.10
TRIGGER26: J80.4, J82.1, U27.8
TRIGGER27: J80.3, U27.2
TRIGGER28: J80.2, U27.5
TRIGGER29: J92.1, U31.10
TRIGGER30: J92.4, J94.1, U31.8
TRIGGER31: J92.3, U31.2
TRIGGER32: J92.2, U31.5
VCCIO: C1.1, C9.1, J1.VCC, R1.2, U2.4
VCCIO1: C11.1, C20.1, J21.VCC, R17.2, U5.4
VCCIO2: C22.1, C30.1, J33.VCC, R27.2, U9.4
VCCIO3: C32.1, C40.1, J45.VCC, R37.2, U13.4
VCCIO4: C42.1, C50.1, J57.VCC, R47.2, U17.4
VCCIO5: C52.1, C60.1, J69.VCC, R57.2, U21.4
VCCIO6: C62.1, C70.1, J81.VCC, R67.2, U25.4
VCCIO7: C72.1, C80.1, J93.VCC, R77.2, U29.4
VOUTL: C3.1, C7.1, U2.1
VOUTL1: C13.1, C18.1, U5.1
VOUTL2: C24.1, C28.1, U9.1
VOUTL3: C34.1, C38.1, U13.1
VOUTL4: C44.1, C48.1, U17.1
VOUTL5: C54.1, C58.1, U21.1
VOUTL6: C64.1, C68.1, U25.1
VOUTL7: C74.1, C78.1, U29.1
VOUTR: C6.1, C8.1, U2.2
VOUTR1: C14.1, C19.1, U5.2
VOUTR2: C25.1, C29.1, U9.2
VOUTR3: C35.1, C39.1, U13.2
VOUTR4: C45.1, C49.1, U17.2
VOUTR5: C55.1, C59.1, U21.2
VOUTR6: C65.1, C69.1, U25.2
VOUTR7: C75.1, C79.1, U29.2

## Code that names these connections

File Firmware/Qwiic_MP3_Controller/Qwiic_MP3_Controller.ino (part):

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#define COMMAND_STOP 0x00
#define COMMAND_PLAY_TRACK 0x01 //Play a given track number like on a CD: regardless of file names plays 2nd file in dir.
#define COMMAND_PLAY_FILENUMBER 0x02 //Play a file # from the root directory: 3 will play F003xxx.mp3
#define COMMAND_PAUSE 0x03 //Will pause if playing, or starting playing if paused
#define COMMAND_PLAY_NEXT 0x04
#define COMMAND_PLAY_PREVIOUS 0x05
#define COMMAND_SET_EQ 0x06
#define COMMAND_SET_VOLUME 0x07
#define COMMAND_GET_SONG_COUNT 0x08 //Note: This causes song to stop playing
#define COMMAND_GET_SONG_NAME 0x09 //Fill global array with 8 characters of the song name
#define COMMAND_GET_PLAY_STATUS 0x0A
#define COMMAND_GET_CARD_STATUS 0x0B
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const byte firmwareVersionMinor = 1;

//Hardware pins
const byte adr = 9; //Address select jumper is on pin 9
const byte trigger1 = 5; //There are four 'trigger' pins used to trigger the playing of a track
const byte trigger2 = 10;
const byte trigger3 = 8;
const byte trigger4 = 3;
const byte interruptOutput = 7;
const byte playing = 2;

//Variables used in the I2C interrupt so we use volatile
volatile byte systemStatus = SYSTEM_STATUS_OK; //Tracks the response from the MP3 IC
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
byte songCount = 0; //Tracks how many songs are available to play
byte oldTriggerNumber = 0; //Tracks trigger state changes
unsigned long lastCheck = 0; //Tracks the last time we checked if song is playing

void setup()
{
  pinMode(adr, INPUT_PULLUP);
  pinMode(playing, INPUT_PULLUP);

  pinMode(trigger1, INPUT_PULLUP);
  pinMode(trigger2, INPUT_PULLUP);
  pinMode(trigger3, INPUT_PULLUP);
  pinMode(trigger4, INPUT_PULLUP);

  //This will set the int pin to high impedance (aka pulled high by external resistor)
  digitalWrite(interruptOutput, LOW); //Push pin to disable internal pull-ups
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    delay(100); //Debounce/Wait a bit in case user is pulling other pins low

    byte fileNumber = 0;
    if (digitalRead(trigger1) == LOW) fileNumber += 1;
    if (digitalRead(trigger2) == LOW) fileNumber += 2;
    if (digitalRead(trigger3) == LOW) fileNumber += 3;
    if (digitalRead(trigger4) == LOW) fileNumber += 4;

    //Is one of the triggers still activated? More debouncing.
    if (fileNumber > 0)
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
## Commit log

2018-04-15 Removing extra files
2018-04-25 Fixed errors. V02 ready
    Added AC caps to headphones. 3.3V now gets through on MP3 IC. 100k swap on amp to make less loud. More decoupling. Fixed trigger numbering.
2018-05-01 Adding basic firmware
2018-05-08 Working code
2018-05-10 Updating readme
2018-05-10 Nearing production code
2018-05-10 Small schematic note change
2018-05-11 Adding examples. Adding readmes.
2018-06-04 Fix for issue 3
2018-06-20 OddCommit
2018-06-20 Revert "OddCommit"
    This reverts commit 5cd89683eb1f2e7621ff14169c194c3af59dd775.
2018-11-19 Readme update to new SKU
2018-11-19 Update to USB C
2018-11-19 File name clean up.
2018-11-19 Fixing product name silk. Adding production panel.
2018-11-29 Routing Playing pin on WS to Shutdown pin on amp
2018-11-29 Rolling to v11 copper
2019-01-12 Adding production panel files for v11 reds
2019-01-16 Remove examples. They live in library now. Remove tester sketch, that's moved to qc vault.
2019-01-16 Bring back ATmega328 debug with gates. Turn off internal pullup when INT goes low.
2019-01-20 File rename. Add GET_ID command.
2019-01-22 Commit for v1.1
2019-01-23 Readme update with new photo and description
2019-01-23 Readme typo fix
2021-11-17 Add batch programming tools
2021-11-17 Add pop reduction component changes from v12.
2021-11-17 Re-route to accommodate H4
2021-11-17 Proto with MY1690
2021-11-17 Add gerbers for v20
2021-11-17 v20 small test panel
2021-11-17 Mute volume to prevent auto-loop bug.
2021-12-14 Add MY1690x datasheet
2021-12-14 Update HEX with auto-play fix.
2021-12-19 Route MY1690X-16S
2022-01-07 Add v20 panel
